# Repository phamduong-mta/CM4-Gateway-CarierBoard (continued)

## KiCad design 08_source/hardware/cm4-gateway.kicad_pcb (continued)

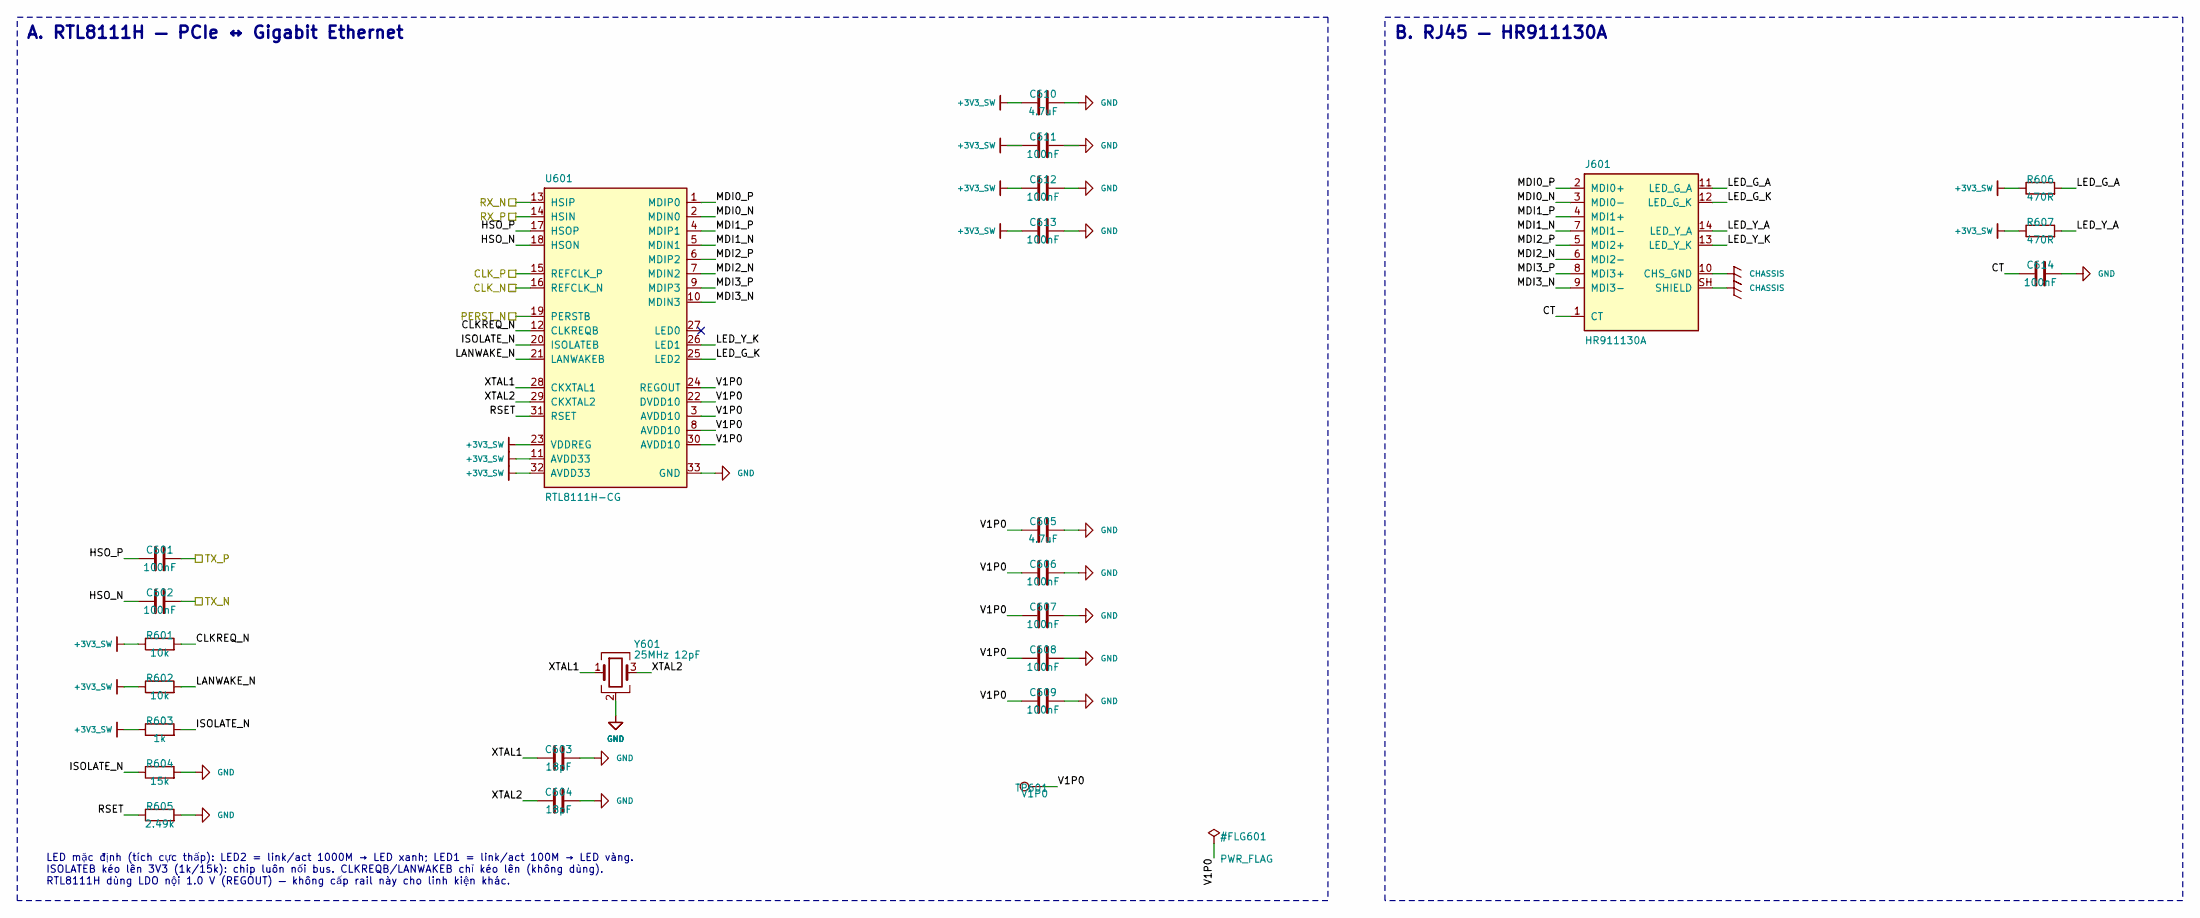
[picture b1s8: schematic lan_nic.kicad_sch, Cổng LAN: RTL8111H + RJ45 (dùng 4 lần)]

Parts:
C601, C602, C606, C607, C608, C609, C611, C612, C613, C614: 100nF; C_0402_1005Metric; MPN CL05B104KO5NNNC; LCSC C1525
C603, C604: 18pF; C_0402_1005Metric; MPN CL05C180JB5NNNC; LCSC C307443
C605, C610: 4.7uF; C_0603_1608Metric; MPN CL10A475KO8NNNC; LCSC C19666
J601: HR911130A; RJ45_Hanrun_HR911130A_Horizontal; MPN HR911130A; LCSC C54408
R601, R602: 10k; R_0402_1005Metric; MPN 0402WGF1002TCE; LCSC C25744
R603: 1k; R_0402_1005Metric; MPN 0402WGF1001TCE; LCSC C11702
R604: 15k; R_0402_1005Metric; MPN 0402WGF1502TCE; LCSC C25756
R605: 2.49k; R_0402_1005Metric; MPN 0402WGF2491TCE; LCSC C25884
R606, R607: 470R; R_0402_1005Metric; MPN 0402WGF4700TCE; LCSC C25117
TP601: V1P0; TestPoint_Pad_D1.0mm
U601: RTL8111H-CG; QFN-32-1EP_4x4mm_P0.4mm_EP2.65x2.65mm; MPN RTL8111H-CG; LCSC C2761340
Y601: 25MHz 12pF; Crystal_SMD_3225-4Pin_3.2x2.5mm; MPN X322525MOB4SI; LCSC C9006

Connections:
+3V3_SW: C610.1, C611.1, C612.1, C613.1, R601.1, R602.1, R603.1, R606.1, R607.1, U601.11 (AVDD33), U601.23 (VDDREG), U601.32 (AVDD33); also elsewhere on the board
/LAN1/CLKREQ_N: R601.2, U601.12 (CLKREQB)
/LAN1/CT: C614.1, J601.1 (CT)
/LAN1/HSO_N: C602.1, U601.18 (HSON)
/LAN1/HSO_P: C601.1, U601.17 (HSOP)
/LAN1/ISOLATE_N: R603.2, R604.1, U601.20 (ISOLATEB)
/LAN1/LANWAKE_N: R602.2, U601.21 (LANWAKEB)
/LAN1/LED_G_A: J601.11 (LED_G_A), R606.2
/LAN1/LED_G_K: J601.12 (LED_G_K), U601.25 (LED2)
/LAN1/LED_Y_A: J601.14 (LED_Y_A), R607.2
/LAN1/LED_Y_K: J601.13 (LED_Y_K), U601.26 (LED1)
/LAN1/MDI0_N: J601.3 (MDI0-), U601.2 (MDIN0)
/LAN1/MDI0_P: J601.2 (MDI0+), U601.1 (MDIP0)
/LAN1/MDI1_N: J601.7 (MDI1-), U601.5 (MDIN1)
/LAN1/MDI1_P: J601.4 (MDI1+), U601.4 (MDIP1)
/LAN1/MDI2_N: J601.6 (MDI2-), U601.7 (MDIN2)
/LAN1/MDI2_P: J601.5 (MDI2+), U601.6 (MDIP2)
/LAN1/MDI3_N: J601.9 (MDI3-), U601.10 (MDIN3)
/LAN1/MDI3_P: J601.8 (MDI3+), U601.9 (MDIP3)
/LAN1/RSET: R605.1, U601.31 (RSET)
/LAN1/V1P0: C605.1, C606.1, C607.1, C608.1, C609.1, TP601.1, U601.3 (AVDD10), U601.8 (AVDD10), U601.22 (DVDD10), U601.24 (REGOUT), U601.30 (AVDD10)
/LAN1/XTAL1: C603.1, U601.28 (CKXTAL1), Y601.1
/LAN1/XTAL2: C604.1, U601.29 (CKXTAL2), Y601.3
CHASSIS: J601.10 (CHS_GND), J601.SH (SHIELD); also elsewhere on the board
GND: C603.2, C604.2, C605.2, C606.2, C607.2, C608.2, C609.2, C610.2, C611.2, C612.2, C613.2, C614.2, R604.2, R605.2, U601.33 (GND), Y601.2 (G), Y601.4 (G); also elsewhere on the board
P1_CLK_N: U601.16 (REFCLK_N); also elsewhere on the board
P1_CLK_P: U601.15 (REFCLK_P); also elsewhere on the board
P1_NIC2SW_N: C602.2; also elsewhere on the board
P1_NIC2SW_P: C601.2; also elsewhere on the board
P1_RST_N: U601.19 (PERSTB); also elsewhere on the board
P1_SW2NIC_N: U601.13 (HSIP); also elsewhere on the board
P1_SW2NIC_P: U601.14 (HSIN); also elsewhere on the board

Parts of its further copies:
C701, C702, C706, C707, C708, C709, C711, C712, C713, C714, C801, C802, C806, C807, C808, C809, C811, C812, C813, C814, C901, C902, C906, C907, C908, C909, C911, C912, C913, C914: 100nF; C_0402_1005Metric; MPN CL05B104KO5NNNC; LCSC C1525
C703, C704, C803, C804, C903, C904: 18pF; C_0402_1005Metric; MPN CL05C180JB5NNNC; LCSC C307443
C705, C710, C805, C810, C905, C910: 4.7uF; C_0603_1608Metric; MPN CL10A475KO8NNNC; LCSC C19666
J701, J801, J901: HR911130A; RJ45_Hanrun_HR911130A_Horizontal; MPN HR911130A; LCSC C54408
R701, R702, R801, R802, R901, R902: 10k; R_0402_1005Metric; MPN 0402WGF1002TCE; LCSC C25744
R703, R803, R903: 1k; R_0402_1005Metric; MPN 0402WGF1001TCE; LCSC C11702
R704, R804, R904: 15k; R_0402_1005Metric; MPN 0402WGF1502TCE; LCSC C25756
R705, R805, R905: 2.49k; R_0402_1005Metric; MPN 0402WGF2491TCE; LCSC C25884
R706, R707, R806, R807, R906, R907: 470R; R_0402_1005Metric; MPN 0402WGF4700TCE; LCSC C25117
TP701, TP801, TP901: V1P0; TestPoint_Pad_D1.0mm
U701, U801, U901: RTL8111H-CG; QFN-32-1EP_4x4mm_P0.4mm_EP2.65x2.65mm; MPN RTL8111H-CG; LCSC C2761340
Y701, Y801, Y901: 25MHz 12pF; Crystal_SMD_3225-4Pin_3.2x2.5mm; MPN X322525MOB4SI; LCSC C9006

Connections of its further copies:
+3V3_SW: C710.1, C711.1, C712.1, C713.1, C810.1, C811.1, C812.1, C813.1, C910.1, C911.1, C912.1, C913.1, R701.1, R702.1, R703.1, R706.1, R707.1, R801.1, R802.1, R803.1, R806.1, R807.1, R901.1, R902.1, R903.1, R906.1, R907.1, U701.11 (AVDD33), U701.23 (VDDREG), U701.32 (AVDD33), U801.11 (AVDD33), U801.23 (VDDREG), U801.32 (AVDD33), U901.11 (AVDD33), U901.23 (VDDREG), U901.32 (AVDD33); also elsewhere on the board
/LAN2/CLKREQ_N: R701.2, U701.12 (CLKREQB)
/LAN2/CT: C714.1, J701.1 (CT)
/LAN2/HSO_N: C702.1, U701.18 (HSON)
/LAN2/HSO_P: C701.1, U701.17 (HSOP)
/LAN2/ISOLATE_N: R703.2, R704.1, U701.20 (ISOLATEB)
/LAN2/LANWAKE_N: R702.2, U701.21 (LANWAKEB)
/LAN2/LED_G_A: J701.11 (LED_G_A), R706.2
/LAN2/LED_G_K: J701.12 (LED_G_K), U701.25 (LED2)
/LAN2/LED_Y_A: J701.14 (LED_Y_A), R707.2
/LAN2/LED_Y_K: J701.13 (LED_Y_K), U701.26 (LED1)
/LAN2/MDI0_N: J701.3 (MDI0-), U701.2 (MDIN0)
/LAN2/MDI0_P: J701.2 (MDI0+), U701.1 (MDIP0)
/LAN2/MDI1_N: J701.7 (MDI1-), U701.5 (MDIN1)
/LAN2/MDI1_P: J701.4 (MDI1+), U701.4 (MDIP1)
/LAN2/MDI2_N: J701.6 (MDI2-), U701.7 (MDIN2)
/LAN2/MDI2_P: J701.5 (MDI2+), U701.6 (MDIP2)
/LAN2/MDI3_N: J701.9 (MDI3-), U701.10 (MDIN3)
/LAN2/MDI3_P: J701.8 (MDI3+), U701.9 (MDIP3)
/LAN2/RSET: R705.1, U701.31 (RSET)
/LAN2/V1P0: C705.1, C706.1, C707.1, C708.1, C709.1, TP701.1, U701.3 (AVDD10), U701.8 (AVDD10), U701.22 (DVDD10), U701.24 (REGOUT), U701.30 (AVDD10)
/LAN2/XTAL1: C703.1, U701.28 (CKXTAL1), Y701.1
/LAN2/XTAL2: C704.1, U701.29 (CKXTAL2), Y701.3
/LAN3/CLKREQ_N: R801.2, U801.12 (CLKREQB)
/LAN3/CT: C814.1, J801.1 (CT)
/LAN3/HSO_N: C802.1, U801.18 (HSON)
/LAN3/HSO_P: C801.1, U801.17 (HSOP)
/LAN3/ISOLATE_N: R803.2, R804.1, U801.20 (ISOLATEB)
/LAN3/LANWAKE_N: R802.2, U801.21 (LANWAKEB)
/LAN3/LED_G_A: J801.11 (LED_G_A), R806.2
/LAN3/LED_G_K: J801.12 (LED_G_K), U801.25 (LED2)
/LAN3/LED_Y_A: J801.14 (LED_Y_A), R807.2
/LAN3/LED_Y_K: J801.13 (LED_Y_K), U801.26 (LED1)
/LAN3/MDI0_N: J801.3 (MDI0-), U801.2 (MDIN0)
/LAN3/MDI0_P: J801.2 (MDI0+), U801.1 (MDIP0)
/LAN3/MDI1_N: J801.7 (MDI1-), U801.5 (MDIN1)
/LAN3/MDI1_P: J801.4 (MDI1+), U801.4 (MDIP1)
/LAN3/MDI2_N: J801.6 (MDI2-), U801.7 (MDIN2)
/LAN3/MDI2_P: J801.5 (MDI2+), U801.6 (MDIP2)
/LAN3/MDI3_N: J801.9 (MDI3-), U801.10 (MDIN3)
/LAN3/MDI3_P: J801.8 (MDI3+), U801.9 (MDIP3)
/LAN3/RSET: R805.1, U801.31 (RSET)
/LAN3/V1P0: C805.1, C806.1, C807.1, C808.1, C809.1, TP801.1, U801.3 (AVDD10), U801.8 (AVDD10), U801.22 (DVDD10), U801.24 (REGOUT), U801.30 (AVDD10)
/LAN3/XTAL1: C803.1, U801.28 (CKXTAL1), Y801.1
/LAN3/XTAL2: C804.1, U801.29 (CKXTAL2), Y801.3
/LAN4/CLKREQ_N: R901.2, U901.12 (CLKREQB)
/LAN4/CT: C914.1, J901.1 (CT)
/LAN4/HSO_N: C902.1, U901.18 (HSON)
/LAN4/HSO_P: C901.1, U901.17 (HSOP)
/LAN4/ISOLATE_N: R903.2, R904.1, U901.20 (ISOLATEB)
/LAN4/LANWAKE_N: R902.2, U901.21 (LANWAKEB)
/LAN4/LED_G_A: J901.11 (LED_G_A), R906.2
/LAN4/LED_G_K: J901.12 (LED_G_K), U901.25 (LED2)
/LAN4/LED_Y_A: J901.14 (LED_Y_A), R907.2
/LAN4/LED_Y_K: J901.13 (LED_Y_K), U901.26 (LED1)
/LAN4/MDI0_N: J901.3 (MDI0-), U901.2 (MDIN0)
/LAN4/MDI0_P: J901.2 (MDI0+), U901.1 (MDIP0)
/LAN4/MDI1_N: J901.7 (MDI1-), U901.5 (MDIN1)
/LAN4/MDI1_P: J901.4 (MDI1+), U901.4 (MDIP1)
/LAN4/MDI2_N: J901.6 (MDI2-), U901.7 (MDIN2)
/LAN4/MDI2_P: J901.5 (MDI2+), U901.6 (MDIP2)
/LAN4/MDI3_N: J901.9 (MDI3-), U901.10 (MDIN3)
/LAN4/MDI3_P: J901.8 (MDI3+), U901.9 (MDIP3)
/LAN4/RSET: R905.1, U901.31 (RSET)
/LAN4/V1P0: C905.1, C906.1, C907.1, C908.1, C909.1, TP901.1, U901.3 (AVDD10), U901.8 (AVDD10), U901.22 (DVDD10), U901.24 (REGOUT), U901.30 (AVDD10)
/LAN4/XTAL1: C903.1, U901.28 (CKXTAL1), Y901.1
/LAN4/XTAL2: C904.1, U901.29 (CKXTAL2), Y901.3
CHASSIS: J701.10 (CHS_GND), J701.SH (SHIELD), J801.10 (CHS_GND), J801.SH (SHIELD), J901.10 (CHS_GND), J901.SH (SHIELD); also elsewhere on the board
GND: C703.2, C704.2, C705.2, C706.2, C707.2, C708.2, C709.2, C710.2, C711.2, C712.2, C713.2, C714.2, C803.2, C804.2, C805.2, C806.2, C807.2, C808.2, C809.2, C810.2, C811.2, C812.2, C813.2, C814.2, C903.2, C904.2, C905.2, C906.2, C907.2, C908.2, C909.2, C910.2, C911.2, C912.2, C913.2, C914.2, R704.2, R705.2, R804.2, R805.2, R904.2, R905.2, U701.33 (GND), U801.33 (GND), U901.33 (GND), Y701.2 (G), Y701.4 (G), Y801.2 (G), Y801.4 (G), Y901.2 (G), Y901.4 (G); also elsewhere on the board
P2_CLK_N: U701.16 (REFCLK_N); also elsewhere on the board
P2_CLK_P: U701.15 (REFCLK_P); also elsewhere on the board
P2_NIC2SW_N: C702.2; also elsewhere on the board
P2_NIC2SW_P: C701.2; also elsewhere on the board
P2_RST_N: U701.19 (PERSTB); also elsewhere on the board
P2_SW2NIC_N: U701.13 (HSIP); also elsewhere on the board
P2_SW2NIC_P: U701.14 (HSIN); also elsewhere on the board
P3_CLK_N: U801.16 (REFCLK_N); also elsewhere on the board
P3_CLK_P: U801.15 (REFCLK_P); also elsewhere on the board
P3_NIC2SW_N: C802.2; also elsewhere on the board
P3_NIC2SW_P: C801.2; also elsewhere on the board
P3_RST_N: U801.19 (PERSTB); also elsewhere on the board
P3_SW2NIC_N: U801.13 (HSIP); also elsewhere on the board
P3_SW2NIC_P: U801.14 (HSIN); also elsewhere on the board
P4_CLK_N: U901.16 (REFCLK_N); also elsewhere on the board
P4_CLK_P: U901.15 (REFCLK_P); also elsewhere on the board
P4_NIC2SW_N: C902.2; also elsewhere on the board
P4_NIC2SW_P: C901.2; also elsewhere on the board
P4_RST_N: U901.19 (PERSTB); also elsewhere on the board
P4_SW2NIC_N: U901.13 (HSIP); also elsewhere on the board
P4_SW2NIC_P: U901.14 (HSIN); also elsewhere on the board

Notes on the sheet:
A. RTL8111H — PCIe ↔ Gigabit Ethernet
LED mặc định (tích cực thấp): LED2 = link/act 1000M → LED xanh; LED1 = link/act 100M → LED vàng. ISOLATEB kéo lên 3V3 (1k/15k): chip luôn nối bus. CLKREQB/LANWAKEB chỉ kéo lên (không dùng). RTL8111H dùng LDO nội 1.0 V (REGOUT) — không cấp rail này cho linh kiện khác.
B. RJ45 — HR911130A

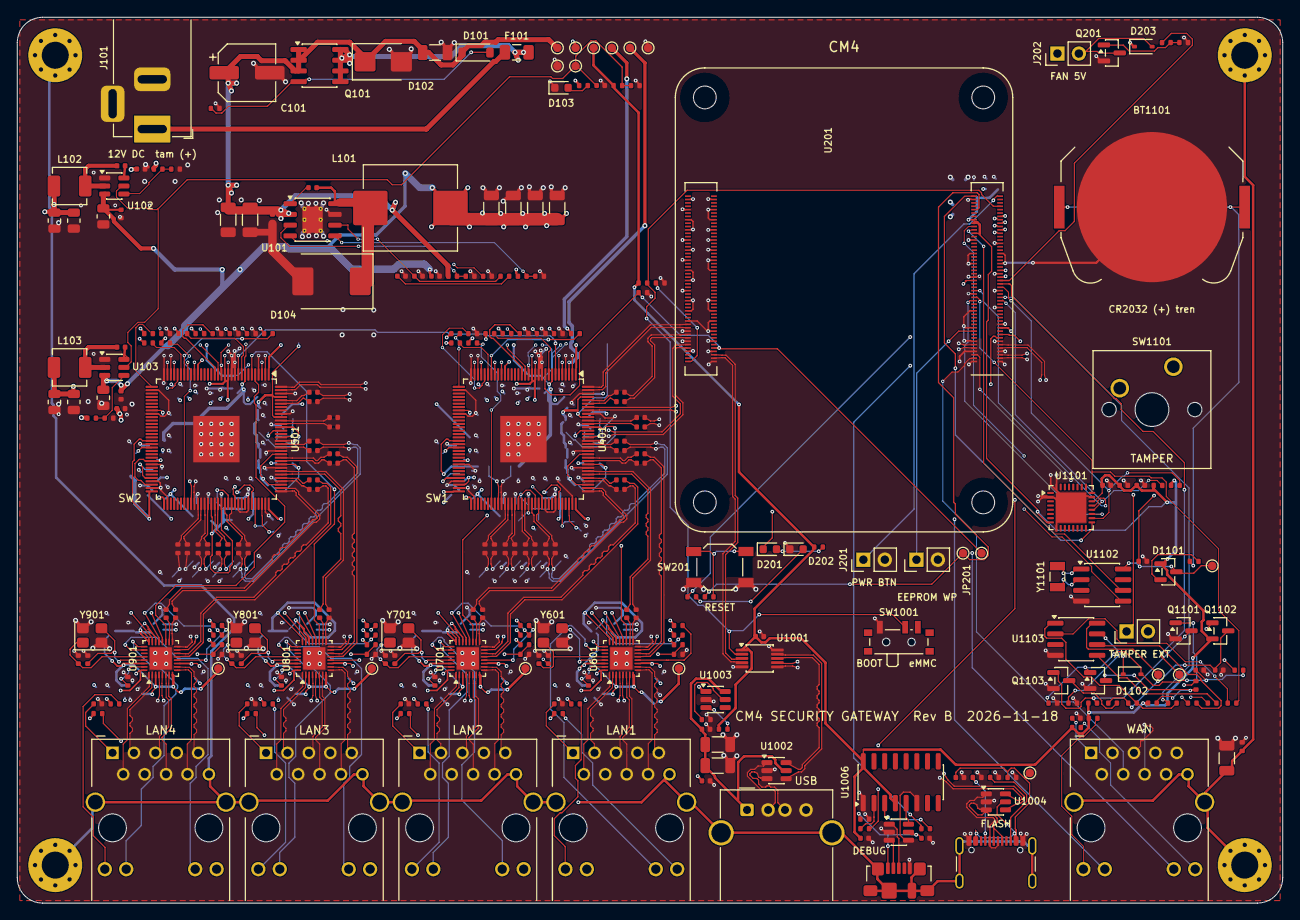
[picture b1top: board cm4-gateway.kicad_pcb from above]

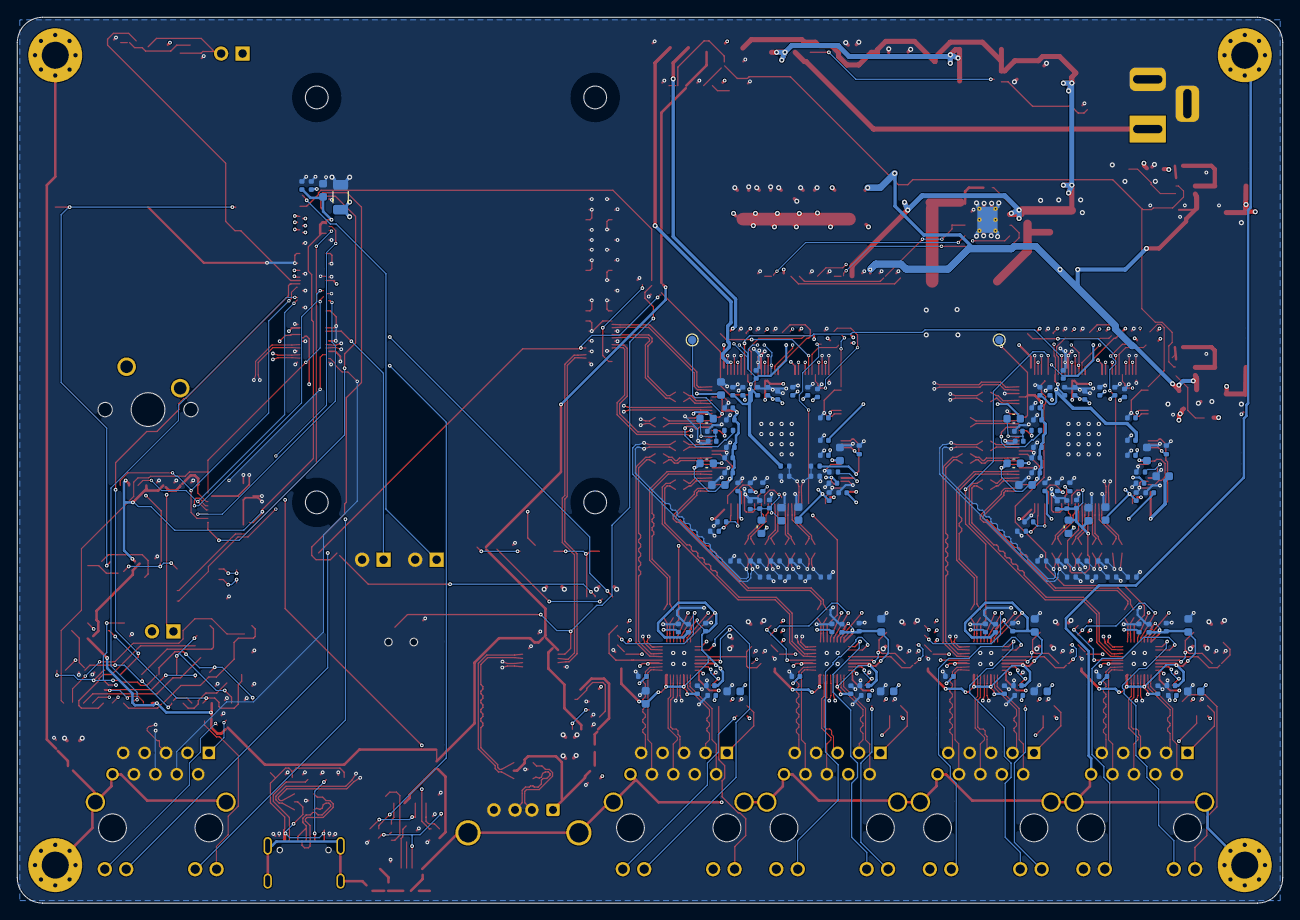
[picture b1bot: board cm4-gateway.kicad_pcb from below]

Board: 6 copper layers, 150.0 x 105.0 mm, 420 parts (144 on the bottom side), 315 nets.

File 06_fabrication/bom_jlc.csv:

Comment,Designator,Footprint,LCSC Part #
CR2032,BT1101,BatteryHolder_Keystone_3034_1x20mm,C5199422
100uF/35V,C101,CP_Elec_6.3x7.7,C176683
10uF/50V,"C102,C104,C105",C_1206_3216Metric,C13585
100nF,"C103,C109,C114,C116,C117,C120,C122,C123,C126,C202,C204,C301,C401,C402,C403,C404,C405,C406,C407,C408,C409,C410,C412,C413,C414,C415,C416,C418,C419,C420,C422,C425,C426,C427,C428,C429,C430,C431,C432,C433,C434,C435,C437,C438,C439,C440,C441,C442,C501,C502,C503,C504,C505,C506,C507,C508,C509,C510,C512,C513,C514,C515,C516,C518,C519,C520,C522,C525,C526,C527,C528,C529,C530,C531,C532,C533,C534,C535,C537,C538,C539,C540,C541,C542,C601,C602,C606,C607,C608,C609,C611,C612,C613,C614,C701,C702,C706,C707,C708,C709,C711,C712,C713,C714,C801,C802,C806,C807,C808,C809,C811,C812,C813,C814,C901,C902,C906,C907,C908,C909,C911,C912,C913,C914,C1001,C1002,C1005,C1006,C1007,C1008,C1101,C1102,C1104,C1106",C_0402_1005Metric,C1525
100nF/50V,C106,C_0402_1005Metric,C77020
4.7nF,C107,C_0402_1005Metric,C84705
47pF,C108,C_0402_1005Metric,C84706
47uF,"C110,C111,C112,C113,C201,C1003,C1004",C_1206_3216Metric,C96123
22uF,"C115,C118,C119,C121,C124,C125",C_0805_2012Metric,C45783
10uF,"C203,C411,C423,C424,C436,C511,C523,C524,C536",C_0603_1608Metric,C19702
4.7nF/2kV,C302,C_1206_3216Metric,C41017
4.7uF,"C417,C517,C605,C610,C705,C710,C805,C810,C905,C910",C_0603_1608Metric,C19666
1uF,"C421,C521,C1103",C_0402_1005Metric,C52923
18pF,"C603,C604,C703,C704,C803,C804,C903,C904",C_0402_1005Metric,C307443
1nF,C1105,C_0402_1005Metric,C14442
BZT52C12,D101,D_SOD-123,C43491
SMBJ24A,D102,D_SMB,C123819
PWR (đỏ),D103,LED_0603_1608Metric,C2286
B560C,D104,D_SMC,C85100
ACT (xanh),D201,LED_0603_1608Metric,C12624
STATUS (xanh),D202,LED_0603_1608Metric,C12624
1N4148WS,"D203,D1102",D_SOD-323,C2128
BAT54C,D1101,SOT-23,C2135
4A 32V,F101,Fuse_1206_3216Metric,C187596
120R@100MHz 2A,"FB401,FB402,FB403,FB501,FB502,FB503",L_0603_1608Metric,C14709
DC-005-5A-2.0,J101,BarrelJack_XKB_DC-005-5A,C381116
PWR_BTN (GLOBAL_EN),J201,PinHeader_1x02_P2.54mm_Vertical,C124375
FAN 5V,J202,PinHeader_1x02_P2.54mm_Vertical,C124375
HR911130A,"J301,J601,J701,J801,J901",RJ45_Hanrun_HR911130A_Horizontal,C54408
USB-A 67643-2910,J1001,USB_A_Molex_67643_Horizontal,C564920
USB4105-GF-A,J1002,USB_C_Receptacle_GCT_USB4105-xx-A_16P_TopMnt_Horizontal,C3020560
micro-USB 47346-0001,J1003,USB_Micro-B_Molex_47346-0001,C132560
TAMPER_EXT (jumper),J1101,PinHeader_1x02_P2.54mm_Vertical,C124375
EEPROM_WP (đóng = khóa ghi),JP201,PinHeader_1x02_P2.54mm_Vertical,C124375
10uH 7.8A,L101,L_Changjiang_FXL1040,C475915
2.2uH 4.5A,"L102,L103",L_Changjiang_FXL0420,C167206
AO4407A,Q101,SOIC-8_3.9x4.9mm_P1.27mm,C16072
AO3400A,Q201,SOT-23,C20917
BSS138,"Q1101,Q1104",SOT-23,C8490
AO3401A,Q1102,SOT-23,C15127
2N7002,Q1103,SOT-23,C8545
100k,"R101,R104,R205,R1005,R1008,R1109",R_0402_1005Metric,C25741
2.2k,R102,R_0402_1005Metric,C25879
10k,"R103,R112,R114,R203,R208,R209,R211,R601,R602,R701,R702,R801,R802,R901,R902,R1001,R1101,R1102,R1107,R1110,R1112",R_0402_1005Metric,C25744
300k,R105,R_0402_1005Metric,C25774
51k,R106,R_0402_1005Metric,C25794
243k,R107,R_0402_1005Metric,C43249
13k,R108,R_0402_1005Metric,C25754
53.6k,R109,R_0402_1005Metric,C53398
10.2k,R110,R_0402_1005Metric,C11660
33.2k,R111,R_0402_1005Metric,C122548
3.4k,R113,R_0402_1005Metric,C4940
470R,"R201,R202,R301,R302,R606,R607,R706,R707,R806,R807,R906,R907,R1006,R1007",R_0402_1005Metric,C25117
0R,R204,R_0402_1005Metric,C17168
220R,R206,R_0402_1005Metric,C25091
100R,R207,R_0402_1005Metric,C25076
1.37k,"R210,R212",R_0402_1005Metric,C423239
1M,R303,R_0402_1005Metric,C26083
1.43k,"R401,R501",R_0402_1005Metric,C11671
475R,"R402,R502",R_0402_1005Metric,C49065
330R,"R403,R421,R424,R425,R426,R427,R431,R432,R503,R521,R524,R525,R526,R527,R531,R532",R_0402_1005Metric,C25104
33R,"R404,R406,R408,R410,R412,R414,R416,R418,R504,R506,R508,R510,R512,R514,R516,R518",R_0402_1005Metric,C25105
49.9R,"R405,R407,R409,R411,R413,R415,R417,R419,R505,R507,R509,R511,R513,R515,R517,R519",R_0402_1005Metric,C25120
5.1k,"R420,R422,R423,R428,R429,R430,R520,R522,R523,R528,R529,R530,R1003,R1004",R_0402_1005Metric,C25905
1k,"R603,R703,R803,R903,R1103,R1104,R1111,R1113,R1114,R1115",R_0402_1005Metric,C11702
15k,"R604,R704,R804,R904",R_0402_1005Metric,C25756
2.49k,"R605,R705,R805,R905",R_0402_1005Metric,C25884
22k,R1002,R_0402_1005Metric,C25768
4.7M,R1105,R_0402_1005Metric,C474132
10M,R1106,R_0402_1005Metric,C26082
10R,R1108,R_0402_1005Metric,C25077
RESET,SW201,SW_SPST_SKQG_WithStem,C115351
BOOT (PCM12),SW1001,SW_SPDT_PCM12,C221841
MX Red (vỏ đậy = đóng),SW1101,SW_Cherry_MX_1.00u_PCB,C49234236
TPS54560BDDAR,U101,HSOP-8-1EP_3.9x4.9mm_P1.27mm_EP2.41x3.1mm_ThermalVias,C1850354
TPS563201DDCR,"U102,U103",TSOT-23-6,C116592
DF40C-100DS-0.4V (CM4),"U201A,U201B",DF40C-100DS-0.4V,C3642394
PI7C9X2G404SL,"U401,U501",LQFP-128-1EP_14x14mm_P0.4mm_EP5.5x5.5mm,C500767
RTL8111H-CG,"U601,U701,U801,U901",QFN-32-1EP_4x4mm_P0.4mm_EP2.65x2.65mm,C2761340
FSUSB42MUX,U1001,MSOP-10_3x3mm_P0.5mm,C11355
USBLC6-2SC6,"U1002,U1004,U1005",SOT-23-6,C7519
TPS2553DBVR,U1003,SOT-23-6,C55266
CH340C,U1006,SOIC-16_3.9x9.9mm_P1.27mm,C84681
SLB9670VQ2.0,U1101,QFN-32-1EP_5x5mm_P0.5mm_EP3.6x3.6mm,C1012863
PCF85063AT,U1102,SOIC-8_3.9x4.9mm_P1.27mm,C5151540
23LCV1024-I/SN,U1103,SOIC-8_3.9x4.9mm_P1.27mm,C615097
25MHz 12pF,"Y601,Y701,Y801,Y901",Crystal_SMD_3225-4Pin_3.2x2.5mm,C9006
32.768kHz 7pF,Y1101,Crystal_SMD_3215-2Pin_3.2x1.5mm,C97604

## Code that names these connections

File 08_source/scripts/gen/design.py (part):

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        20: "EEPROM_nWP", 21: "LED_nACT",
        24: "NC", 25: "NC", 26: "NC", 27: "NC", 28: "NC", 29: "NC", 30: "NC", 31: "NC",   # GPIO26,21,19,20,13,16,6,12
        34: "NC", 35: "NC", 36: "NC",                                                      # GPIO5, ID_SC, ID_SD
        37: "TPM_CS_N", 38: "SPI_SCLK", 39: "SRAM_CS_N", 40: "SPI_MISO", 41: "NC",        # GPIO7,11,8,9,25
        44: "SPI_MOSI", 45: "TPM_PIRQ_N", 46: "NC", 47: "TAMPER_OPEN", 48: "NC",          # GPIO10,24,22,23,27
        49: "FAN_PWM", 50: "LED_STATUS", 51: "UART_RXD", 54: "NC", 55: "UART_TXD",        # GPIO18,17,15,4,14
        56: "NC", 58: "NC",                                                                 # GPIO3, GPIO2
        57: "NC", 61: "NC", 62: "NC", 63: "NC", 64: "NC", 67: "NC", 68: "NC", 69: "NC", 70: "NC", 72: "NC",
        73: "NC", 75: "NC", 76: "NC",
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    c.tp("RUN_PG", X0 + 22, 68)
    c.tp("PCIE_RST_N", X0 + 8, 68)

    sh.frame((X0 - 4) * G, 75 * G, (X0 + 34) * G, 104 * G, "Quạt 5 V (tùy chọn, PWM GPIO18)")
    c.g("fan")
    c.part("HDR2", "FAN 5V", X0 + 8, 82, {"1": "+5V", "2": ".FAN_N"}, prefix="J")
    qf = c.part("AO3400A", "AO3400A", X0 + 20, 82, {"G": ".FAN_G", "D": ".FAN_N", "S": "GND"})
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            "TMS": ".TMS", "TRST_L": ".TRST"})
    u2.nc("VC1_EN", "RXPOLINV_DIS", "PL_512B", "PRSNT1", "PRSNT2", "PRSNT3",
          "SLOT_IMP1", "SLOT_IMP2", "SLOT_IMP3", "EECLK", "SCAN_EN",
          "GPIO0", "GPIO1", "GPIO2", "GPIO3", "GPIO4", "GPIO5", "GPIO6", "GPIO7",
          "PORTSTATUS0", "PORTSTATUS1", "PORTSTATUS2", "TCK", "TDO", "TDI", "NC")
    c.g("strap").at(100, 92)
    c.R("5.1k", "+3V3_SW", ".SLOTCLK")
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    sh.text("VBUS của USB-C KHÔNG nối vào rail +5V của bo (tránh máy tính cấp ngược).\n"
            "Khi nạp eMMC, bo vẫn cấp nguồn bằng jack 12 V.", 10 * G, 110 * G, size=1.3)

    sh.frame(82 * G, 60 * G, 160 * G, 112 * G, "D. Console UART — micro-USB → CH340C → GPIO14/15")
    c.g("dbg")
    jm = c.ic("Connector:USB_B_Micro", "micro-USB 47346-0001", 94, 78, FP["MICROUSB"], "C132560",
              "47346-0001", prefix="J")
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    c.g("tpm")
    t = c.ic(symdefs.slb9670(), "SLB9670VQ2.0", 32, 34, FP["TPM"], "C1012863", "SLB9670VQ20FW785XTMA1")
    t.net({"CS#": "TPM_CS_N", "SCLK": "SPI_SCLK", "MOSI": "SPI_MOSI", "MISO": "SPI_MISO",
           "RST#": "nEXTRST", "PIRQ#": "TPM_PIRQ_N", "GPIO": "NC", "PP": "NC",
           "VDD": "+3V3", "GND": "GND", "NC": "NC", "NCI": "NC"})
    c.at(62, 16)
    c.R("10k", "+3V3", "TPM_CS_N")
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    c.C("100nF", "0402", "+3V3", "GND")
    c.C("100nF", "0402", "+3V3", "GND")
    c.C("1uF", "0402", "+3V3", "GND")
    sh.text("overlay: dtoverlay=tpm-slb9670 (SPI0, CE1 = GPIO7).\nRST# nối nEXTRST của CM4.", 10 * G, 58 * G, size=1.3)

    sh.frame(82 * G, 8 * G, 160 * G, 60 * G, "B. RTC PCF85063A + pin CR2032 (rail V_KEEP)")
    c.g("rtc")
    r = c.ic(symdefs.rtc(), "PCF85063AT", 106, 22, FP["SO8"], "C5151540", "PCF85063AT/AY")
    r.net({"OSCI": ".RTC_XI", "OSCO": ".RTC_XO", "SCL": "RTC_SCL", "SDA": "RTC_SDA",
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    c.flag(".V_KEEP", 150, 46)
    c.flag(".VBAT", 140, 46)
    c.tp(".V_KEEP", 100, 52)
    sh.text("V_KEEP = OR(+3V3, pin): nuôi RTC và nhánh tamper. Khi CM4 có điện, pin không bị tiêu hao.\n"
            "overlay: dtoverlay=i2c-rtc,pcf85063a,i2c_csi_dsi (SDA0/SCL0 = GPIO44/45).", 84 * G, 58.5 * G, size=1.3)

    sh.frame(8 * G, 64 * G, 160 * G, 112 * G, "C. Chống mở vỏ: MX switch → cắt nguồn + kẹp GND SRAM 23LCV1024")
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    c.tp("TAMPER_OPEN", 100, 94)
    sh.text("Vỏ đậy: MX đóng → V_SW ≈ V_KEEP → Q1101 dẫn → VCC_GATE thấp → Q1102 cấp +3V3 cho SRAM; D1102 nạp chân VBAT (giữ dữ liệu khi mất điện).\n"
            "Mở vỏ / đứt dây / rút jumper: V_SW xả qua 4.7 MΩ (τ ≈ 5 ms) → Q1101 tắt → VCC_GATE lên +3V3 (10 k) → Q1102 ngắt, Q1103 kẹp SRAM_VCC qua 10 Ω;\n"
            "VBAT_SRAM mất nguồn (D1102 chặn dòng rò ngược về V_SW, xả qua 10 MΩ + dòng VBAT). Q1104 tạo TAMPER_OPEN riêng → mạch xóa KHÔNG phụ thuộc trạng thái GPIO23.\n"
            "Điện trở nối tiếp trên CS/SCK/SI/SO chặn dòng ký sinh từ bus SPI vào SRAM đã bị ngắt.",
            10 * G, 111 * G, size=1.25)
    return sh
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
